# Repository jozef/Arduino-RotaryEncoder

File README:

NAME

    RotaryEncoder.h/cpp - read/decode/count rotary encoder pulses

SYNOPSIS

        #include <Arduino.h>
        #include <RotaryEncoder.h>      // https://github.com/jozef/Arduino-RotaryEncoder
    
        const uint8_t pin_a = 2; const uint8_t pin_b = 4; const uint8_t pin_btn = 7;
    
        RotaryEncoder rote(pin_a,pin_b,pin_btn);
    
        void setup () {
            rote.setup();
            Serial.begin(9600);
        }
    
        void loop () {
            if (rote.btn_pressed()) {
                // switch is pressed
                Serial.println("switch pressed");
                rote.counter = 0;
            }
            if (rote.changed()) {
                Serial.println(rote.counter);
                if (rote.counter > 0) {
                    // more steps CW then CCW
                }
            }
            delay(200);
        }

DESCRIPTION

    Arduino class/library to read-out one or more rotary encoders.

    See examples/ folder for schematics and example usage.

 PROPERTIES

    int counter:

    number of rotation steps

    int8_t direction:

    -1 for counter clockwise, 0 for one step reversed to the previous
    direction or 1 for clockwise turning.

    int limit_min; int limit_max:

    minimum and maximum value that counter can have. if both are the same
    value, no limit.

    int step:

    how much is a single rotational step. by default 1.

    uint8_t pin_a:

    Arduino pin on which encoder pin A is connected. If the pin supports
    interrupt, update() function is called automatically.

    uint8_t pin_b:

    Arduino pin on which encoder pin B is connected.

    uint8_t pin_btn:

    Arduino pin on which encoder push button is connected.

 METHODS

    RotaryEncoder(uint8_t a, uint8_t b, uint8_t btn = 0, int init_counter =
    0):

    Constructor, a and b pins are required. Button pin and initial value
    for counter optional.

    void setup():

    Will initiate pins and interrupts.

    bool update():

    Needs to be called as "fast as possible" if Arduino pin connected to
    encoder pin A is not on an interrupt pin to update state and do the
    counting.

    bool changed():

    Set to true if there was any change to the counter since the last call
    of this function.

    bool btn_pressed():

    Returns true/false if button is pressed.

EXAMPLES

 examples/RotaryEncoder_single/RotaryEncoder_synopsis.ino

    Code from SYNOPSIS section.

 examples/RotaryEncoder_single/RotaryEncoder_single.ino

    Print rotary counted value on serial port and light up led.
    Brighten/Dimm led based on rotary counter.

INSTALL

        git clone https://github.com/jozef/Arduino-RotaryEncoder.git sketchbook/libraries/RotaryEncoder

SEE ALSO

    https://blog.kutej.net/2019/01/rotary-encoder
    https://hackaday.com/2015/12/09/embed-with-elliot-debounce
    http://www.labbookpages.co.uk/electronics/debounce.html

LICENSE

    This is free software, licensed under the MIT License.

AUTHOR

        Jozef Kutej

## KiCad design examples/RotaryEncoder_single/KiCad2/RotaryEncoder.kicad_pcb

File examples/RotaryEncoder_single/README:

NAME

    RotaryEncoder_single.ino - print rotary encoder data on serial port and
    brighten/dimm led.

DESCRIPTION

    When turning the rotary encoder clock wise will add-up to the counter
    and increase the brightness of the led. Once maximum value is reached
    the led will start blinking. On counterclockwise will decrease the
    counter and once below zero will start to blink. Pushing the button
    will light-up the led to maximum intensity. And print out counter
    status to the serial port.

        pin 2 → A pin
        pin 4 → B pin
        pin 7 → Button pin
        pin 10 → led + resistor

HARDWARE

    See KiCad schematics and image in current folder.

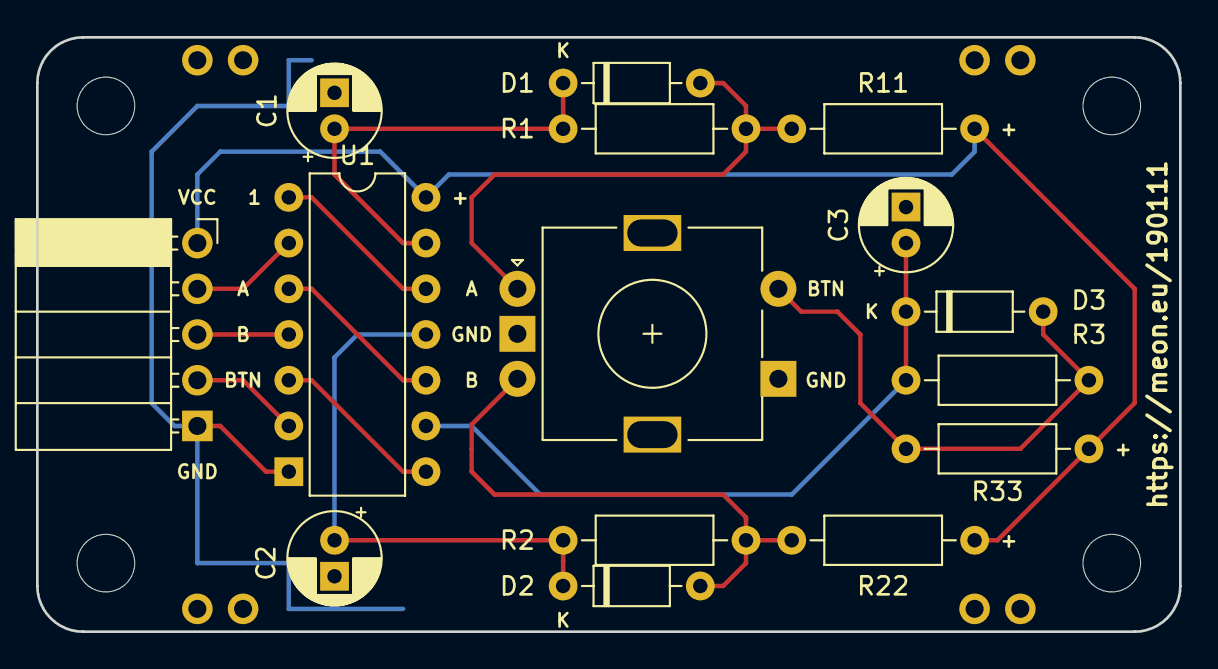
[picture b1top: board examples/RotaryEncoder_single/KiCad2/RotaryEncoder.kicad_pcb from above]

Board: 2 copper layers, 63.5 x 33.0 mm, 15 parts (0 on the bottom side), 14 nets.

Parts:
C1, C2, C3: 0.1ųF; CP_Radial_D5.0mm_P2.00mm
D1, D2, D3: 1N4148; D_DO-35_SOD27_P7.62mm_Horizontal
J1: Conn_01x05; PinSocket_1x05_P2.54mm_Horizontal
R1, R2, R3, R11, R22, R33: 10k; R_Axial_DIN0207_L6.3mm_D2.5mm_P10.16mm_Horizontal
SW1: Rotary Encoder Switch; RotaryEncoder_Alps_EC11E-Switch_Vertical_H20mm
U1: 74HC14; DIP-14_W7.62mm

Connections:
GND: C1.2, C2.2, C3.2, J1.5, SW1.C, SW1.S1, U1.7
unnamed: C1.1, D1.1, R1.1, U1.13
unnamed: C2.1, D2.1, R2.1, U1.11
unnamed: C3.1, D3.1, R3.1, U1.9
unnamed: D1.2, R1.2, R11.2, SW1.A
unnamed: D2.2, R2.2, R22.2, SW1.B
unnamed: D3.2, R3.2, R33.2, SW1.S2
unnamed: J1.2, U1.2
unnamed: J1.3, U1.4
unnamed: J1.4, U1.6
unnamed: U1.1, U1.12
unnamed: U1.5, U1.8
unnamed: U1.3, U1.10
VCC: J1.1, R11.1, R22.1, R33.1, U1.14

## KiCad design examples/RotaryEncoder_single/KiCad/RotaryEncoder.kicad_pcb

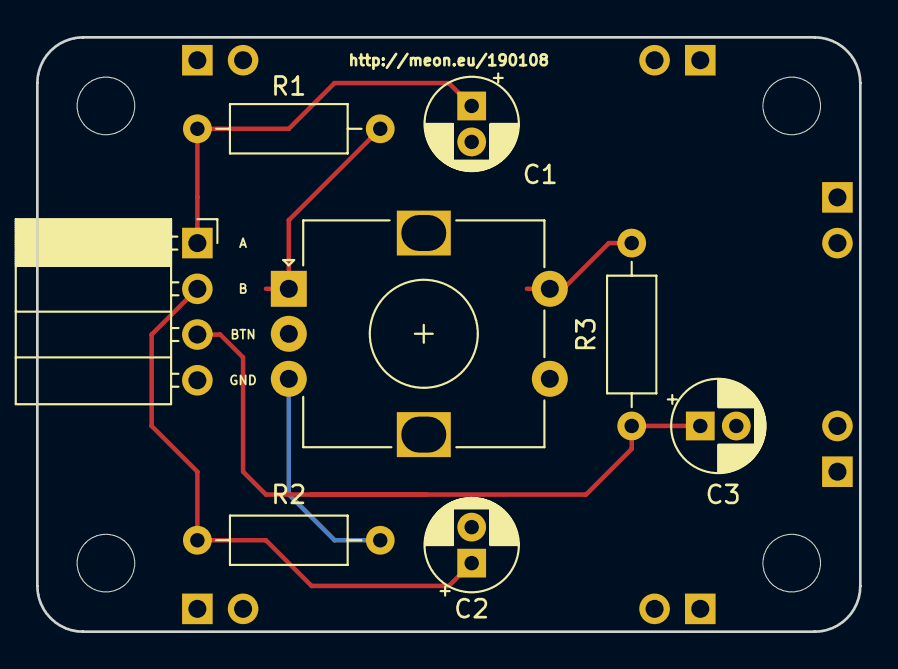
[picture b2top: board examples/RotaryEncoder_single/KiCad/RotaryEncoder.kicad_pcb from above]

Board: 2 copper layers, 45.7 x 33.0 mm, 8 parts (0 on the bottom side), 7 nets.

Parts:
C1, C2, C3: 0.1ųF; CP_Radial_D5.0mm_P2.00mm
P1: CONN_01X04; PinSocket_1x04_P2.54mm_Horizontal
R1, R2, R3: 22k; R_Axial_DIN0207_L6.3mm_D2.5mm_P10.16mm_Horizontal
SW1: Rotary_Encoder_Switch; RotaryEncoder_Alps_EC12E-Switch_Vertical_H20mm

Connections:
unnamed: C1.1, P1.1, R1.1
unnamed: C1.2, C2.2, C3.2, P1.4, SW1.C, SW1.S2
unnamed: C2.1, P1.2, R2.1
unnamed: C3.1, P1.3, R3.1
unnamed: R1.2, SW1.A
unnamed: R2.2, SW1.B
unnamed: R3.2, SW1.S1

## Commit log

2019-01-08 initial
2019-01-12 add second kicad design
2019-01-26 use double negation to have same signals between v1 and v2
2019-02-10 two rotary encoders example
